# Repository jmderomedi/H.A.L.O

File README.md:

### TechSafari2018 ###
For AU Tech Safari 2018, we are tasked to create a data visualization website/presentation. The first task at hand is to create
the hardware that will collect the data. After some discussions we deciced upon GPS data and environmental data. The device is able
to take data at set increments that is choosen by potentiometer. The data will than be saved to an SD card and parsed. The parsing will clean the data for the map API that we used. The map API will display an interactive map of every data point and locations of interest that we visited.

This repo only contains the hardware/firmware of the project. See oneyanshi for the front end and complete website.

### Hardware Side ###
The data collection device G-PATH (Gps, Pressure, Altitude, Tempature, Humidity).\n
The device should be Set-and-Forget.\n
Make sure the battery is charged, once plugged in the device will run until the battery dies.

### Built With ###
	-Teensyduino, A plug in for Arduino
	-Adafruit Ultimite GPS Breakout
	-Adafruit SD Breakout
	-Adafruit BME680 (Environmental Sensor)
### Authors ###
	James Deromedi
	
### License ###
This is a free-ware at the moment. Please just reconize the author(s) if you use anything posted here

### Acknowledgements ###
Kristof for being our advisor
John for being the amazing sponsor and setting up this whole trip and event

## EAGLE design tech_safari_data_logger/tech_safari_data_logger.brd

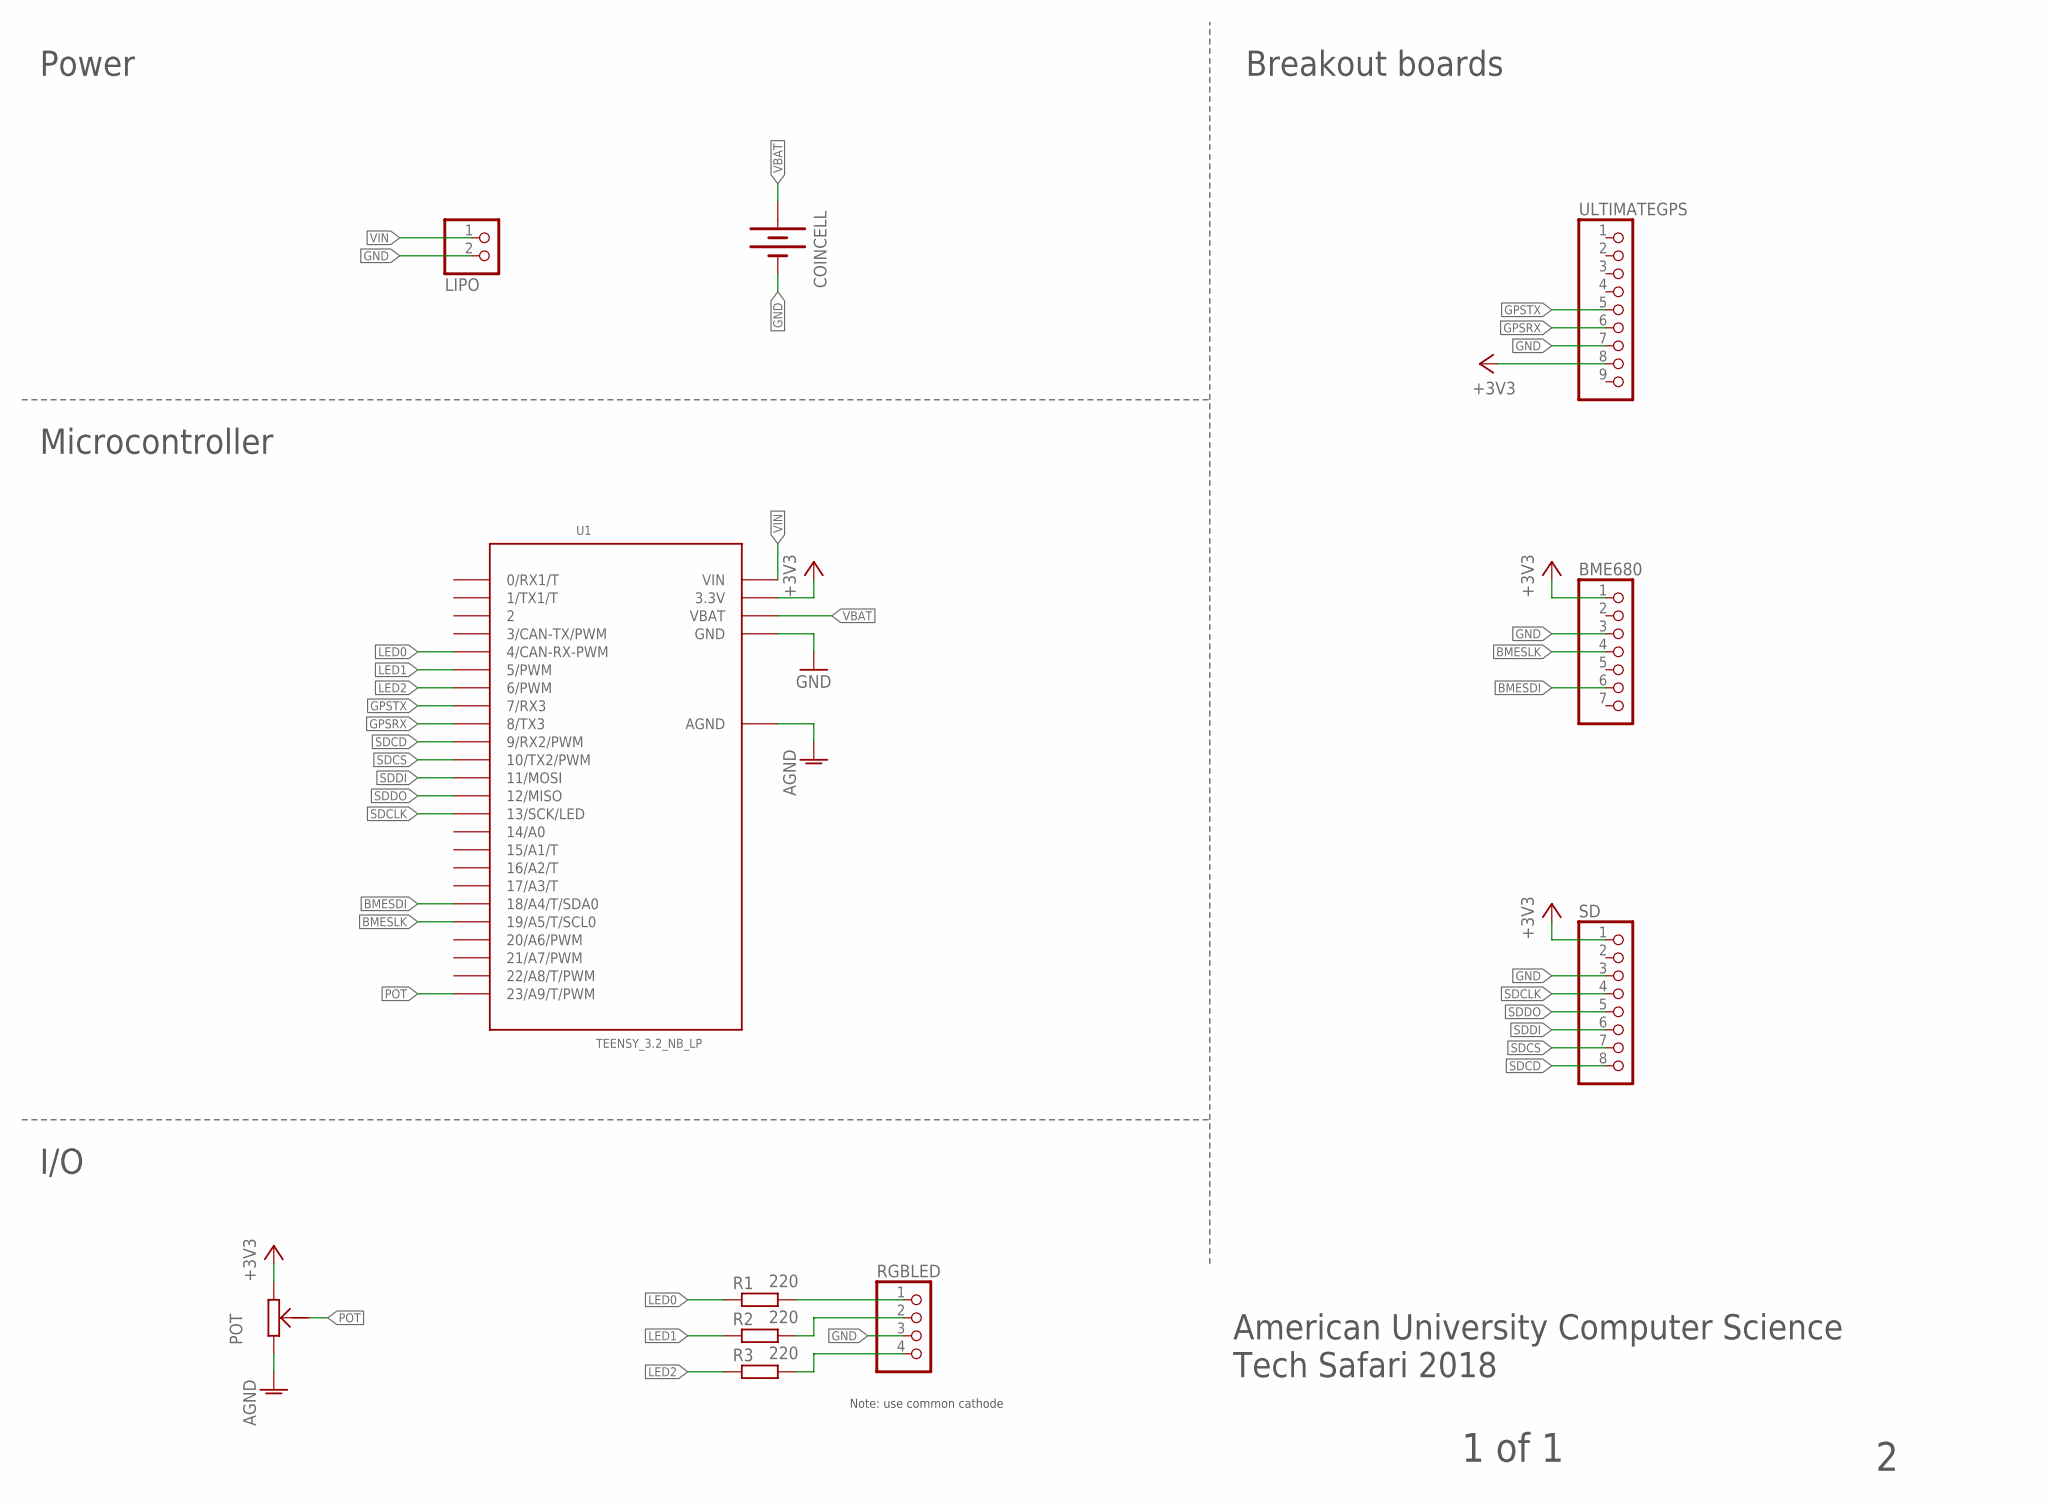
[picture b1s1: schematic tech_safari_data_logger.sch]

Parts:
BME680: PINHD-1X7; 1X07
COINCELL: BATTERY; BATTCON_20MM_SMALL
LIPO: JST_2PIN-THM-RA; JST-PH-2-THM-RA
POT: POTENTIOMETER_THRU
R1, R2, R3: 220; 0207/10
RGBLED: PINHD-1X4; 1X04
SD: PINHD-1X8; 1X08
U1: TEENSY_3.2_NB_LP; TEENSY_3.2__NB_LP
ULTIMATEGPS: PINHD-1X9; 1X09

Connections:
+3V3: BME680.1, POT.3, SD.1, U1.3.3V, ULTIMATEGPS.8
AGND: POT.1, U1.AGND
BMESDI: BME680.6, U1.18/A4 (18/A4/T/SDA0)
BMESLK: BME680.4, U1.19/A5 (19/A5/T/SCL0)
GND: BME680.3, COINCELL.NEG (-), LIPO.2 (1), RGBLED.3, SD.3, U1.GND, ULTIMATEGPS.7
GPSRX: U1.8 (8/TX3), ULTIMATEGPS.6
GPSTX: U1.7 (7/RX3), ULTIMATEGPS.5
LED0: R1.1, U1.4 (4/CAN-RX-PWM)
LED1: R2.1, U1.5 (5/PWM)
LED2: R3.1, U1.6 (6/PWM)
unnamed: R1.2, RGBLED.1
unnamed: R2.2, RGBLED.2
unnamed: R3.2, RGBLED.4
POT: POT.2, U1.23/A9 (23/A9/T/PWM)
SDCD: SD.8, U1.9 (9/RX2/PWM)
SDCLK: SD.4, U1.13 (13/SCK/LED)
SDCS: SD.7, U1.10 (10/TX2/PWM)
SDDI: SD.6, U1.11 (11/MOSI)
SDDO: SD.5, U1.12 (12/MISO)
VBAT: COINCELL.1 (+), COINCELL.2 (+), COINCELL.3 (+), COINCELL.4 (+), U1.VBAT
VIN: LIPO.1 (2), U1.VIN

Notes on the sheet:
Note: use common cathode
1 of 1
American University Computer Science Tech Safari 2018
I/O
Microcontroller
Power
Breakout boards

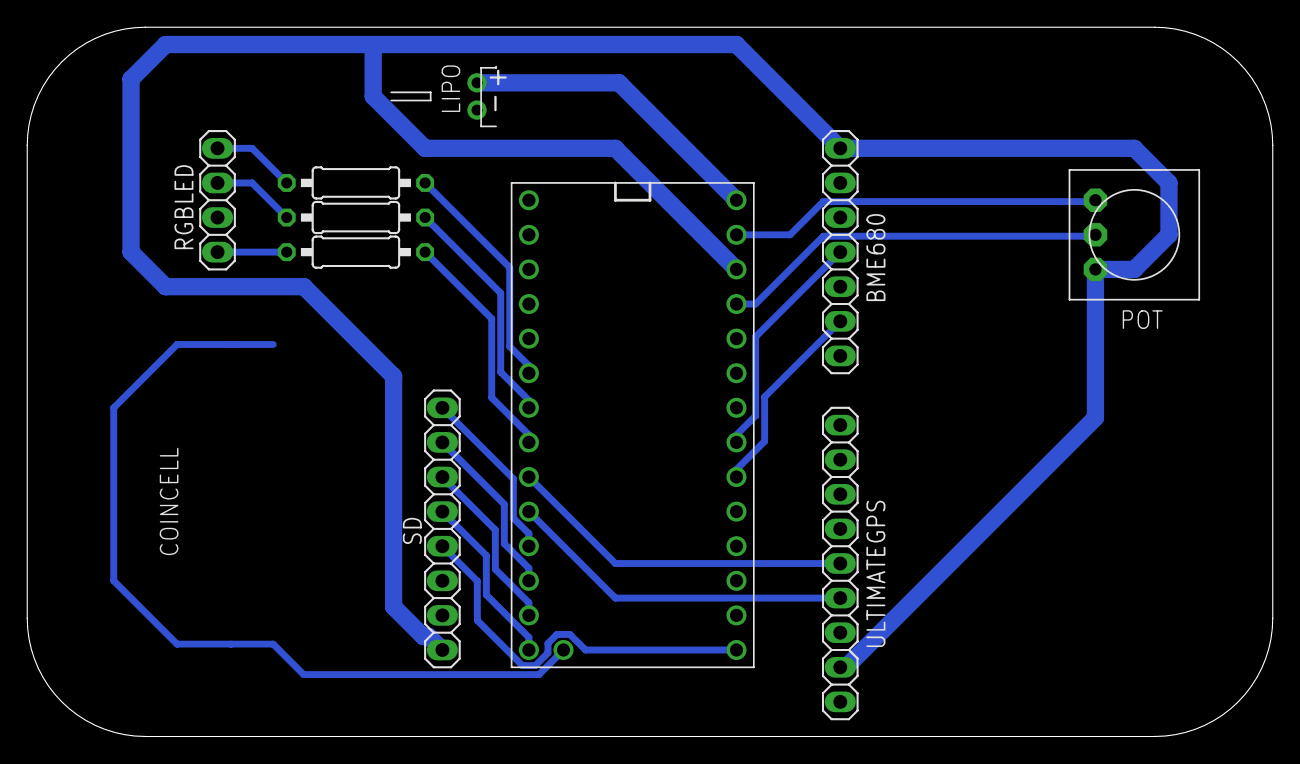
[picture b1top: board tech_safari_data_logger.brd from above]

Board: 2 copper layers, 91.4 x 52.1 mm, 11 parts (1 on the bottom side), 21 nets.

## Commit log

2018-02-28 Framework for DataCollections
2018-02-28 README.md edited
2018-02-28 Debugged timer; Added better documentation
2018-02-28 Added framework for power saving
2018-03-01 Added Snooze.h, letting the chip sleep when not in use
2018-03-01 Added LED functionality
2018-03-01 Added calibration method, Added method to allow unplugging SD card while running
2018-03-01 Added test method, fixed bugs with having SD card pulled out
2018-03-01 Some comment fixing
2018-03-09 DONE! GPS now properly takes data and stores it in SD
2018-03-11 added board designs and .gitignore
2018-03-13 Code used for data collection
2018-03-14 Updated running code, changed control flow of GPS writing
2018-03-15 swapped GPS/SD positions for no overlap
2018-03-16 cleaned up layout of sch and brd
2018-03-16 added pdfs of sch and brd
